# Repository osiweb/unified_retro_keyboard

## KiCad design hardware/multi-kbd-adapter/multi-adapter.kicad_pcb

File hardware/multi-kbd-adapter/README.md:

# Unified Keyboard Project Multi Adapter

This is a keyboard adapter to permit use of Apple 1, Apple 2, and Sol-20
compatible keyboards with any of these three computers.

## Notes
- Protoboard-style pad matrix permits flexible choice of on-board RESET and CLEAR (OR
  LOCAL) switches.
- Pin header allows external RESET and CLEAR (or LOCAL) switches
- Note that the SOL and Apple keyboards have different strobe polarity. Make
  sure the strobe polarity on the keyboard is properly configured.

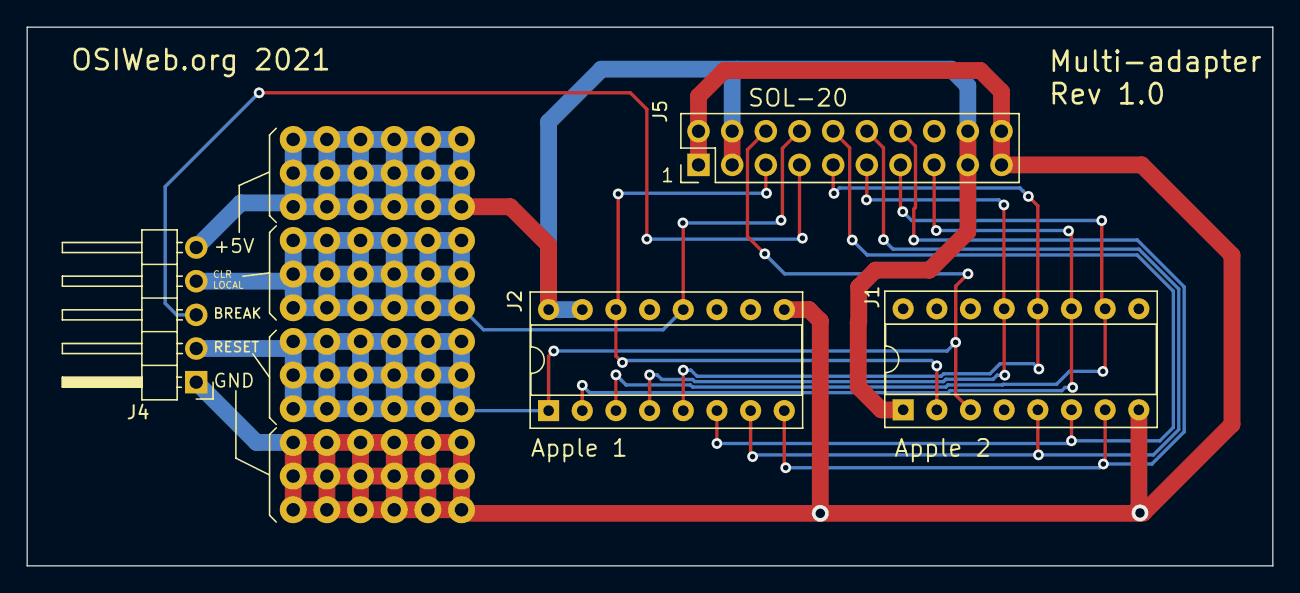
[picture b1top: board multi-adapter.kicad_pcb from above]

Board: 2 copper layers, 94.0 x 40.6 mm, 4 parts (0 on the bottom side), 13 nets.

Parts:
J1: Apple 2; DIP-16_W7.62mm_Socket
J2: Apple 1; DIP-16_W7.62mm_Socket
J4: Outputs; PinHeader_1x05_P2.54mm_Horizontal
J5: SOL-20; SOL20-header-vertical

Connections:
/BREAK: J4.3, J5.4
/CLR-LOCAL: J2.12, J4.4, J5.14
/D0: J1.12, J2.5, J5.5
/D1: J1.13, J2.4, J5.6
/D2: J1.10, J2.3, J5.7
/D3: J1.11, J2.2, J5.8
/D4: J1.6, J2.6, J5.15
/D5: J1.5, J2.7, J5.16
/D6: J1.7, J2.8, J5.17
/~RESET: J1.3, J2.1, J4.2, J5.13
/~STROBE: J1.2, J2.14, J5.3
GND: J1.8, J2.9, J4.1, J5.1, J5.10, J5.11, J5.20
VCC: J1.1, J2.15, J2.16, J4.5, J5.2, J5.9, J5.12, J5.19

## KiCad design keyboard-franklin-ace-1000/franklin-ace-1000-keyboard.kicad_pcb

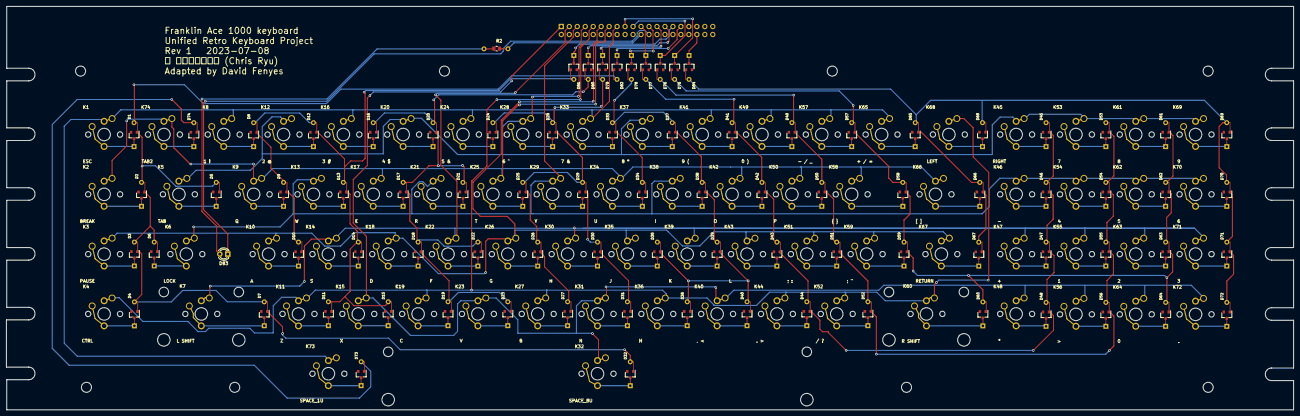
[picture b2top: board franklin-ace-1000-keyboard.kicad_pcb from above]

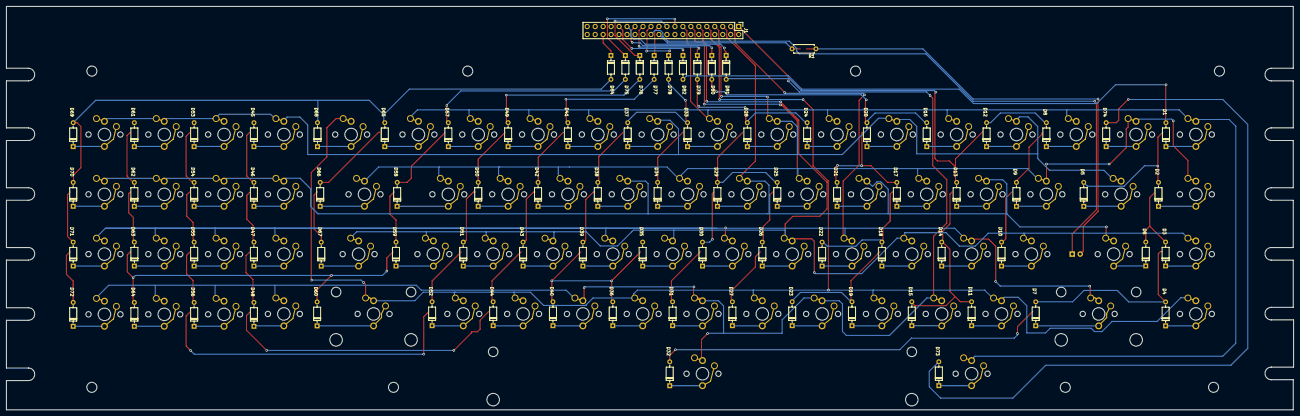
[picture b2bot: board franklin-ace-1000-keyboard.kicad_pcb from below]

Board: 2 copper layers, 410.0 x 128.5 mm, 161 parts (2 on the bottom side), 104 nets.

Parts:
D1, D2, D3, D4, D5, D6, D7, D8, D9, D10, D11, D12, D13, D14, D15, D16, D17, D18, D19, D20, D21, D22, D23, D24, D25, D26, D27, D28, D29, D30, D31, D32, D33, D34, D35, D36, D37, D38, D39, D40, D41, D42, D43, D44, D45, D46, D47, D48, D49, D50, D51, D52, D53, D54, D55, D56, D57, D58, D59, D60, D61, D62, D63, D64, D65, D66, D67, D68, D69, D70, D71, D72, D73, D74: diode-combined
D75, D76, D77, D78, D79, D80, D81, D82, D84: 1N4148; diode-combined
D83: LED; LED_D3.0mm
J1: Conn_02x20_Odd_Even; PinHeader_2x20_P2.54mm_Vertical
K1: ESC; Key_MX
K2: BREAK; Key_MX
K3: PAUSE; Key_MX
K4: CTRL; Key_MX
K5: TAB; Key_MX
K6: LOCK; Key_MX
K7: L SHIFT; Key_MX_2u
K8: 1 !; Key_MX
K9: Q; Key_MX
K10: A; Key_MX
K11: Z; Key_MX
K12: 2 @; Key_MX
K13: W; Key_MX
K14: S; Key_MX
K15: X; Key_MX
K16: 3 #; Key_MX
K17: E; Key_MX
K18: D; Key_MX
K19: C; Key_MX
K20: 4 $; Key_MX
K21: R; Key_MX
K22: F; Key_MX
K23: V; Key_MX
K24: 5 &; Key_MX
K25: T; Key_MX
K26: G; Key_MX
K27: B; Key_MX
K28: 6 ^; Key_MX
K29: Y; Key_MX
K30: H; Key_MX
K31: N; Key_MX
K32: SPACE_8U; Key_MX_Spacebar_5.25
K33: 7 &; Key_MX
K34: U; Key_MX
K35: J; Key_MX
K36: M; Key_MX
K37: 8 *; Key_MX
K38: I; Key_MX
K39: K; Key_MX
K40: , <; Key_MX
K41: 9 (; Key_MX
K42: O; Key_MX
K43: L; Key_MX
K44: . >; Key_MX
K45: RIGHT; Key_MX
K46: -; Key_MX
K47: +; Key_MX
K48: *; Key_MX
K49: 0 ); Key_MX
K50: P; Key_MX
K51: ; :; Key_MX
K52: / ?; Key_MX
K53: 7; Key_MX
K54: 4; Key_MX
K55: 1; Key_MX
K56: >; Key_MX
K57: - / _; Key_MX
K58: { }; Key_MX
K59: ; "; Key_MX
K60: R SHIFT; Key_MX_2u
K61: 8; Key_MX
K62: 5; Key_MX
K63: 2; Key_MX
K64: 0; Key_MX
K65: + / =; Key_MX
K66: [ ]; Key_MX
K67: RETURN; Key_MX
K68: LEFT; Key_MX
K69: 9; Key_MX
K70: 6; Key_MX
K71: 3; Key_MX
K72: .; Key_MX
K73: SPACE_1U; Key_MX
K74: TAB2; Key_MX
R1: 330 ohms; R_Axial_DIN0207_L6.3mm_D2.5mm_P7.62mm_Horizontal
R2: RES 330 ohm 1% MLCC 0805 Yageo; R_0805_2012Metric

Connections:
Col0: J1.15, K1.1, K8.1, K16.1, K24.1, K33.1, K41.1, K49.1, K57.1, K65.1, K73.1
Col1: J1.13, K2.1, K9.1, K17.1, K25.1, K34.1, K42.1, K50.1, K58.1, K66.1, K74.1
Col2: J1.11, K3.1, K10.1, K18.1, K26.1, K35.1, K43.1, K51.1, K59.1, K67.1
Col3: J1.9, K4.1, K11.1, K19.1, K27.1, K36.1, K44.1, K52.1, K60.1, K68.1
Col4: J1.7, K5.1, K12.1, K20.1, K28.1, K37.1, K45.1, K53.1, K61.1, K69.1
Col5: J1.5, K6.1, K13.1, K21.1, K29.1, K38.1, K46.1, K54.1, K62.1, K70.1
Col6: J1.3, K7.1, K14.1, K22.1, K30.1, K39.1, K47.1, K55.1, K63.1, K71.1
Col7: J1.1, K15.1, K23.1, K31.1, K32.1, K40.1, K48.1, K56.1, K64.1, K72.1
unnamed: D1.1 (K), K1.2
unnamed: D2.1 (K), K2.2
unnamed: D3.1 (K), K3.2
unnamed: D4.1 (K), K4.2
unnamed: D5.1 (K), K5.2
unnamed: D6.1 (K), K6.2
unnamed: D7.1 (K), K7.2
unnamed: D8.1 (K), K8.2
unnamed: D9.1 (K), K9.2
unnamed: D10.1 (K), K10.2
unnamed: D11.1 (K), K11.2
unnamed: D12.1 (K), K12.2
unnamed: D13.1 (K), K13.2
unnamed: D14.1 (K), K14.2
unnamed: D15.1 (K), K15.2
unnamed: D16.1 (K), K16.2
unnamed: D17.1 (K), K17.2
unnamed: D18.1 (K), K18.2
unnamed: D19.1 (K), K19.2
unnamed: D20.1 (K), K20.2
unnamed: D21.1 (K), K21.2
unnamed: D22.1 (K), K22.2
unnamed: D23.1 (K), K23.2
unnamed: D24.1 (K), K24.2
unnamed: D25.1 (K), K25.2
unnamed: D26.1 (K), K26.2
unnamed: D27.1 (K), K27.2
unnamed: D28.1 (K), K28.2
unnamed: D29.1 (K), K29.2
unnamed: D30.1 (K), K30.2
unnamed: D31.1 (K), K31.2
unnamed: D32.1 (K), K32.2
unnamed: D33.1 (K), K33.2
unnamed: D34.1 (K), K34.2
unnamed: D35.1 (K), K35.2
unnamed: D36.1 (K), K36.2
unnamed: D37.1 (K), K37.2
unnamed: D38.1 (K), K38.2
unnamed: D39.1 (K), K39.2
unnamed: D40.1 (K), K40.2
unnamed: D41.1 (K), K41.2
unnamed: D42.1 (K), K42.2
unnamed: D43.1 (K), K43.2
unnamed: D44.1 (K), K44.2
unnamed: D45.1 (K), K45.2
unnamed: D46.1 (K), K46.2
unnamed: D47.1 (K), K47.2
unnamed: D48.1 (K), K48.2
unnamed: D49.1 (K), K49.2
unnamed: D50.1 (K), K50.2
unnamed: D51.1 (K), K51.2
unnamed: D52.1 (K), K52.2
unnamed: D53.1 (K), K53.2
unnamed: D54.1 (K), K54.2
unnamed: D55.1 (K), K55.2
unnamed: D56.1 (K), K56.2
unnamed: D57.1 (K), K57.2
unnamed: D58.1 (K), K58.2
unnamed: D59.1 (K), K59.2
unnamed: D60.1 (K), K60.2
unnamed: D61.1 (K), K61.2
unnamed: D62.1 (K), K62.2
unnamed: D63.1 (K), K63.2
unnamed: D64.1 (K), K64.2
unnamed: D65.1 (K), K65.2
unnamed: D66.1 (K), K66.2
unnamed: D67.1 (K), K67.2
unnamed: D68.1 (K), K68.2
unnamed: D69.1 (K), K69.2
unnamed: D70.1 (K), K70.2
unnamed: D71.1 (K), K71.2
unnamed: D72.1 (K), K72.2
unnamed: D73.1 (K), K73.2
unnamed: D74.1 (K), K74.2
unnamed: D75.1 (K), J1.17
unnamed: D76.1 (K), J1.19
unnamed: D77.1 (K), J1.21
unnamed: D78.1 (K), J1.23
unnamed: D79.1 (K), J1.25
unnamed: D80.1 (K), J1.27
unnamed: D81.1 (K), J1.29
unnamed: D82.1 (K), J1.31
unnamed: D83.2 (A), R1.1, R2.1
unnamed: D83.1 (K), J1.24
unnamed: D84.1 (K), J1.36
unnamed: J1.22, R1.2, R2.2
Row0: D1.2 (A), D2.2 (A), D3.2 (A), D4.2 (A), D5.2 (A), D6.2 (A), D7.2 (A), D32.2 (A), D82.2 (A)
Row1: D8.2 (A), D9.2 (A), D10.2 (A), D11.2 (A), D12.2 (A), D13.2 (A), D14.2 (A), D15.2 (A), D81.2 (A)
Row2: D16.2 (A), D17.2 (A), D18.2 (A), D19.2 (A), D20.2 (A), D21.2 (A), D22.2 (A), D23.2 (A), D80.2 (A)
Row3: D24.2 (A), D25.2 (A), D26.2 (A), D27.2 (A), D28.2 (A), D29.2 (A), D30.2 (A), D31.2 (A), D79.2 (A)
Row4: D33.2 (A), D34.2 (A), D35.2 (A), D36.2 (A), D37.2 (A), D38.2 (A), D39.2 (A), D40.2 (A), D78.2 (A)
Row5: D41.2 (A), D42.2 (A), D43.2 (A), D44.2 (A), D45.2 (A), D46.2 (A), D47.2 (A), D48.2 (A), D77.2 (A)
Row6: D49.2 (A), D50.2 (A), D51.2 (A), D52.2 (A), D53.2 (A), D54.2 (A), D55.2 (A), D56.2 (A), D76.2 (A)
Row7: D57.2 (A), D58.2 (A), D59.2 (A), D60.2 (A), D61.2 (A), D62.2 (A), D63.2 (A), D64.2 (A), D75.2 (A)
Row9: D65.2 (A), D66.2 (A), D67.2 (A), D68.2 (A), D69.2 (A), D70.2 (A), D71.2 (A), D72.2 (A), D84.2 (A)
Row10: D73.2 (A), D74.2 (A)

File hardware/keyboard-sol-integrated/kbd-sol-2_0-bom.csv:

Comment,Designator,Footprint,LCSC
36pf,"C1,C2",Capacitor_SMD:C_0603_1608Metric,C134070
0.1 uF,"C3,C4,C5,C6,C7",Capacitor_SMD:C_0603_1608Metric,C14663
1N4148,"D1,D2,D3,D4,D5,D6,D7,D8,D9,D10,D11,D12,D13,D14,D15,D16,D17,D18,D19,D20,D21,D22,D23,D24,D25,D26,D27,D28,D29,D30,D31,D32,D33,D34,D35,D36,D37,D38,D39,D40,D41,D42,D43,D44,D45,D46,D47,D48,D49,D50,D51,D52,D53,D54,D55,D56,D57,D58,D59,D60,D61,D62,D63,D64,D65,D66,D67,D68,D69,D70,D71,D72,D73,D74,D75,D76,D77,D78,D79,D80,D81,D82,D83,D84,D85, D86,D87,D88,D89,D90,D91,D92,D93",unikbd:diode-combined,C118751
330,"R4,R5,R6",Resistor_SMD:R_0805_2012Metric,
10k,R7,Resistor_SMD:R_0603_1608Metric,C98220
ATmega2560-16AU,U1,Package_QFP:TQFP-100_14x14mm_P0.5mm,C22460
16.000 MHz,Y1,Crystal:Crystal_SMD_HC49-SD,C326544
